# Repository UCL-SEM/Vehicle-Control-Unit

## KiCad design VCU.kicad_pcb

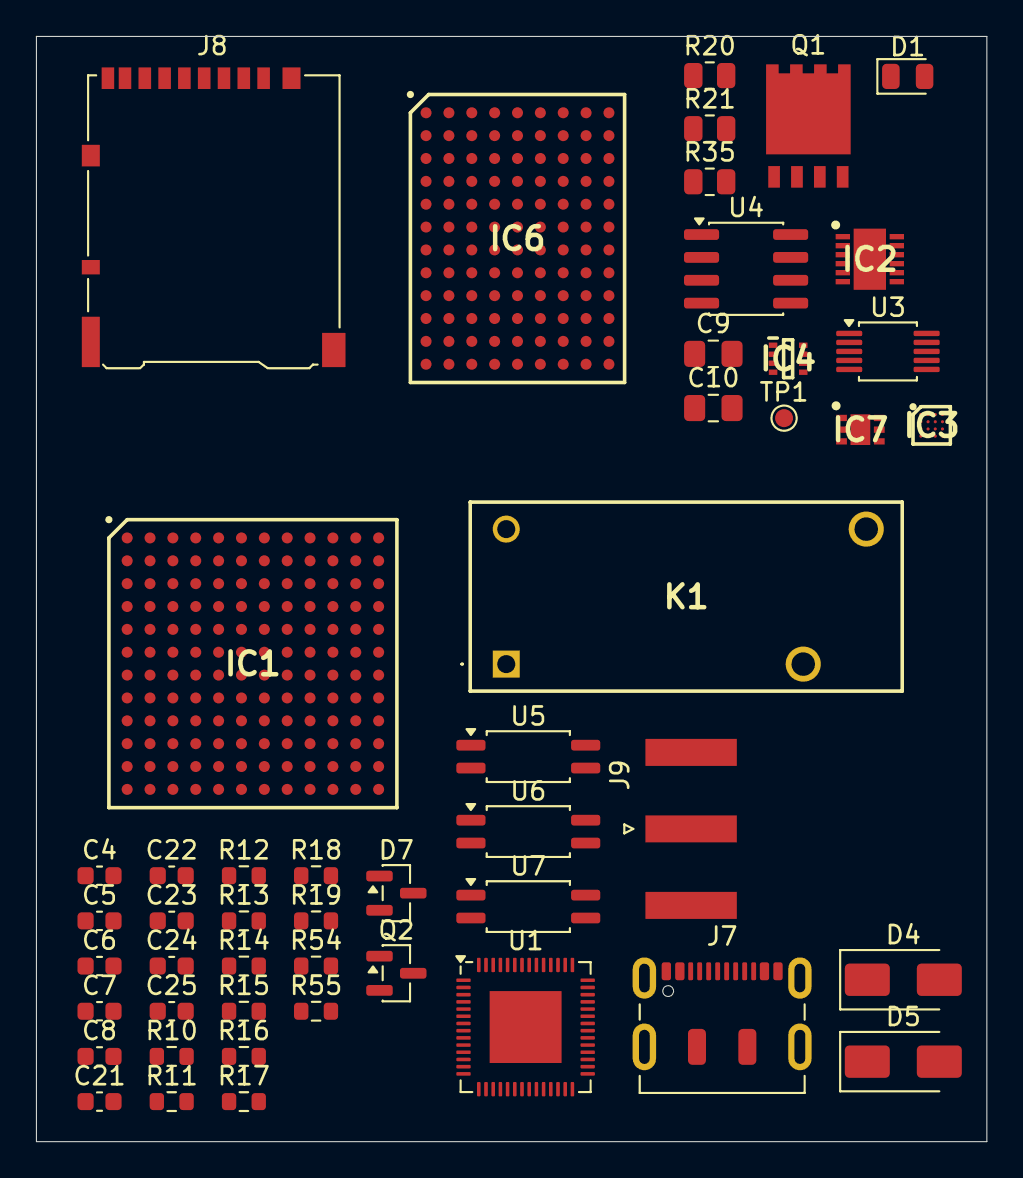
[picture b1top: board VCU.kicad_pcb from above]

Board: 2 copper layers, 52.8 x 61.4 mm, 50 parts (0 on the bottom side), 40 nets, no tracks yet.

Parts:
C4, C21, C24: 10uF; C_0603_1608Metric
C5, C6, C22, C23: 0.1uF; C_0603_1608Metric
C7, C8: 22uF; C_0603_1608Metric
C9: 0.1u; C_0805_2012Metric_Pad1.18x1.45mm_HandSolder
C10: 10u; C_0805_2012Metric_Pad1.18x1.45mm_HandSolder
C25: 47uF; C_0603_1608Metric
D1: LED; LED_0805_2012Metric
D4, D5: M7; D_SMA
D7: T24CAN; SOT-23
IC1: LTM4712IY#PBF; BGA144C127P12X12_1600X1600X868
IC2: LT4363IDE-1_PBF; SON50P300X400X80-13N-D
IC3: INA4235AIYBJR; BGA16C40P4X4_160X160X35
IC4: TPS2117DRLR; SOTFL50P160X60-8N
IC6: LTM8064IY; BGA108C127P9X12_1190X1600X512
IC7: TPS70933DRVR; SON65P200X200X80-7N
J7: DX07S016JA1R1500; USB_C_Receptacle_JAE_DX07S016JA1R1500
J8: DM3AT-SF-PEJM5; microSD_HC_Hirose_DM3AT-SF-PEJM5
J9: 132289; SMA_Amphenol_132289_EdgeMount
K1: G5PZ-1A-X_DC12; G5PZ1AXDC12
Q1: ISC015N06NM5LF2; PG-TDSON-8-FL
Q2: IRLML6344TRPBF; SOT-23
R10, R11: 5.1k; R_0603_1608Metric
R12, R13: 100k; R_0603_1608Metric
R14: 2.2k; R_0603_1608Metric
R15, R16, R17, R18, R19: 10k; R_0603_1608Metric
R20: 10k; R_0805_2012Metric
R21: 1k; R_0805_2012Metric
R35: 10M; R_0805_2012Metric
R54, R55: 60; R_0603_1608Metric
TP1: VBUS; TestPoint_Pad_D1.0mm
U1: ESP32-S3; QFN-56-1EP_7x7mm_P0.4mm_EP4x4mm
U3: INA238; TSSOP-10_3x3mm_P0.5mm
U4: ISO1640; SOIC-8_3.9x4.9mm_P1.27mm
U5, U6, U7: LTV-217-B-G; SOP-4_4.4x2.6mm_P1.27mm

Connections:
+3.3V: C4.1, C6.1, C7.1, C8.1, C23.1, C24.1, J8.4 (VDD), R15.1, R16.1, R17.1, R18.1, R19.1
+3V3: IC3.A4 (VS), IC3.B3 (EN), U4.1 (VCC1), U5.4, U6.4, U7.4
+5V: C21.1, C22.1
+13V: IC1.B4 (EXTVCC), IC6.H1 (VOUT), IC6.H2 (VOUT_1), IC6.H3 (VOUT_1), IC6.H4 (VOUT_1), IC6.J1 (VOUT_1), IC6.J2 (VOUT_1), IC6.J3 (VOUT_1), IC6.J4 (VOUT_1), IC6.K1 (VOUT_1), IC6.K2 (VOUT_1), IC6.K3 (VOUT_1), IC6.K4 (VOUT_1), IC6.L1 (VOUT_1), IC6.L2 (VOUT_1), IC6.L3 (VOUT_1), IC6.L4 (VOUT_1), IC6.M1 (VOUT_1), IC6.M2 (VOUT_1), IC6.M3 (VOUT_1), IC6.M4 (VOUT_1)
/FC_AUX: IC3.D2 (IN-4), IC6.A4 (RUN), IC6.A5 (VIN), IC6.A6 (VIN_1), IC6.A7 (VIN_1), IC6.A8 (VIN_1), IC6.A9 (VIN_1), IC6.B5 (VIN_1), IC6.B6 (VIN_1), IC6.B7 (VIN_1), IC6.B8 (VIN_1), IC6.B9 (VIN_1)
/FC_AUX_SNS+: IC3.D1 (IN+3), IC3.D3 (IN+4)
/FC_IN: IC1.A4 (ISP), IC2.2 (OUT), IC2.3 (SNS), Q1.1 (S)
/FC_SNS-: IC2.5 (VCC), IC2.8 (UV), IC3.A2 (IN-1), Q1.5 (D)
/H2_TTL: R21.1, U7.1
/MISO: J8.7 (DAT0), R19.2
/MOSI: J8.3 (CMD), R18.2
/RG_SNS+: IC1.H11 (VOUT), IC1.H12 (VOUT_2), IC1.J11 (VOUT_3), IC1.J12 (VOUT_4), IC1.K11 (VOUT_5), IC1.K12 (VOUT_6), IC1.L11 (VOUT_7), IC1.L12 (VOUT_8), IC1.M11 (VOUT_9), IC1.M12 (VOUT_10), IC3.A1 (IN+2)
/SCL: IC3.C4 (SCL), U4.3 (SCL1)
/SC_OUT: IC3.C1 (IN-3), K1.2 (COM)
/SDA: IC3.D4 (SDA), U4.2 (SDA1)
/SD_CS: J8.2 (DAT3/CD), R17.2
/SD_DET: C5.1, J8.9 (DET_B), J8.10 (DET_A), R15.2
/USB1_N: J7.A7 (D-), J7.B7 (D-)
/USB1_P: J7.A6 (D+), J7.B6 (D+)
/VBUS: J7.A4 (VBUS), J7.A9 (VBUS), J7.B4 (VBUS), J7.B9 (VBUS), R12.1, R14.1, TP1.1 (1_1)
/VBUS_DET: R12.2, R13.1
AUX_3V3: IC7.1 (OUT), U3.6 (VS), U4.8 (VCC2)
AUX_12V: C9.1, C10.1, IC7.6 (IN), U3.8 (Vbus), U3.9 (Vin-)
AUX_12V-S: D4.1 (K), D5.1 (K), K1.1 (COIL_1), U5.1
AUX_GND: C9.2, C10.2, IC7.3 (GND), IC7.7 (GND_2), Q2.2 (S), R20.2, R35.1, U3.7 (GND), U4.5 (GND2)
GND: C4.2, C5.2, C6.2, C7.2, C8.2, C21.2, C22.2, C23.2, C24.2, C25.2, D1.1 (K), D7.3 (A), IC1.A1 (GND), IC1.A2 (GND_2), IC1.A9 (PHMODE), IC1.A12 (GND_3), IC1.B1 (GND_4), IC1.B2 (GND_5), IC1.B7 (SGND), IC1.B12 (GND_6), IC1.C1 (GND_7), IC1.C2 (GND_8), IC1.C3 (GND_9), IC1.C4 (GND_10), IC1.C5 (GND_11), IC1.C6 (SGND_2), IC1.C7 (SGND_3), IC1.C8 (GND_12), IC1.C9 (GND_13), IC1.C10 (GND_14), IC1.C11 (GND_15), IC1.C12 (GND_16), IC1.D1 (GND_17), IC1.D2 (GND_18), IC1.D3 (GND_19), IC1.D4 (GND_20), IC1.D5 (GND_21), IC1.D6 (SGND_4), IC1.D7 (SGND_5), IC1.D8 (GND_22), IC1.D9 (GND_23), IC1.D10 (GND_24), IC1.D11 (GND_25), IC1.D12 (GND_26), IC1.E1 (GND_27), IC1.E2 (GND_28), IC1.E3 (GND_29), IC1.E4 (GND_30), IC1.E5 (GND_31), IC1.E6 (GND_32), IC1.E7 (GND_33), IC1.E8 (GND_34), IC1.E9 (GND_35), IC1.E10 (GND_36), IC1.E11 (GND_37), IC1.E12 (GND_38), IC1.F1 (GND_39), IC1.F2 (GND_40), IC1.F3 (GND_41), IC1.F4 (GND_42), IC1.F5 (GND_43), IC1.F6 (GND_44), IC1.F7 (GND_45), IC1.F8 (GND_46), IC1.F9 (GND_47), IC1.F10 (GND_48), IC1.F11 (GND_49), IC1.F12 (GND_50), IC1.G1 (GND_51), IC1.G2 (GND_52), IC1.G3 (GND_53), IC1.G4 (GND_54), IC1.G5 (GND_55), IC1.G6 (GND_56), IC1.G7 (GND_57), IC1.G8 (GND_58), IC1.G9 (GND_59), IC1.G10 (GND_60), IC1.G11 (GND_61), IC1.G12 (GND_62), IC1.H3 (GND_63), IC1.H4 (GND_64), IC1.H5 (GND_65), IC1.H6 (GND_66), IC1.H7 (GND_67), IC1.H8 (GND_68), IC1.H9 (GND_69), IC1.H10 (GND_70), IC1.J3 (GND_71), IC1.J4 (GND_72), IC1.J5 (GND_73), IC1.J6 (GND_74), IC1.J7 (GND_75), IC1.J8 (GND_76), IC1.J9 (GND_77), IC1.J10 (GND_78), IC1.K3 (GND_79), IC1.K4 (GND_80), IC1.K6 (GND_81), IC1.K7 (GND_82), IC1.K9 (GND_83), IC1.K10 (GND_84), IC1.L3 (GND_85), IC1.L4 (GND_86), IC1.L6 (GND_87), IC1.L7 (GND_88), IC1.L9 (GND_89), IC1.L10 (GND_90), IC1.M3 (GND_91), IC1.M4 (GND_92), IC1.M5 (GND_93), IC1.M6 (GND_94), IC1.M7 (GND_95), IC1.M8 (GND_96), IC1.M9 (GND_97), IC1.M10 (GND_98), IC2.7 (GND), IC2.9 (GND), IC2.13 (GND), IC3.B4 (GND), IC6.A1 (GND), IC6.B3 (GND_1), IC6.B4 (GND_1), IC6.C2 (GND_1), IC6.C3 (GND_1), IC6.C4 (GND_1), IC6.C5 (GND_1), IC6.C6 (GND_1), IC6.C7 (GND_1), IC6.C8 (GND_1), IC6.C9 (GND_1), IC6.D2 (GND_1), IC6.D3 (GND_1), IC6.D4 (GND_1), IC6.D5 (GND_1), IC6.D6 (GND_1), IC6.D7 (GND_1), IC6.D8 (GND_1), IC6.D9 (GND_1), IC6.E3 (GND_1), IC6.E4 (GND_1), IC6.E5 (GND_1), IC6.E6 (GND_1), IC6.E7 (GND_1), IC6.E8 (GND_1), IC6.E9 (GND_1), IC6.F1 (SYNC), IC6.F2 (MODE), IC6.F3 (GND_1), IC6.F4 (GND_1), IC6.F5 (GND_1), IC6.F6 (GND_1), IC6.F7 (GND_1), IC6.F8 (GND_1), IC6.F9 (GND_1), IC6.G1 (GND_1), IC6.G2 (GND_1), IC6.G3 (GND_1), IC6.G4 (GND_1), IC6.G5 (GND_1), IC6.G6 (GND_1), IC6.G7 (GND_1), IC6.G8 (GND_1), IC6.G9 (GND_1), IC6.H5 (GND_1), IC6.H6 (GND_1), IC6.H7 (GND_1), IC6.H8 (GND_1), IC6.H9 (GND_1), IC6.J5 (GND_1), IC6.J6 (GND_1), IC6.J7 (GND_1), IC6.J8 (GND_1), IC6.J9 (GND_1), IC6.K5 (GND_1), IC6.K6 (GND_1), IC6.K7 (GND_1), IC6.K8 (GND_1), IC6.K9 (GND_1), IC6.L5 (GND_1), IC6.L6 (GND_1), IC6.L7 (GND_1), IC6.L8 (GND_1), IC6.L9 (GND_1), IC6.M5 (GND_1), IC6.M6 (GND_1), IC6.M7 (GND_1), IC6.M8 (GND_1), IC6.M9 (GND_1), J7.A1 (GND), J7.A12 (GND), J7.B1 (GND), J7.B12 (GND), J8.6 (VSS), J9.2 (Ext), R10.2, R11.2, R13.2, R35.2, U1.57 (GND), U4.4 (GND1)
unnamed: C25.1, R54.2, R55.2
unnamed: D1.2 (A), R14.2
unnamed: D4.2 (A), D5.2 (A), K1.4 (COIL_2), Q2.3 (D)
unnamed: IC1.B10 (COMPA), IC1.B11 (COMPB)
unnamed: IC1.A3 (ISN), IC1.H1 (VIN), IC1.H2 (VIN_2), IC1.J1 (VIN_3), IC1.J2 (VIN_4), IC1.K1 (VIN_5), IC1.K2 (VIN_6), IC1.L1 (VIN_7), IC1.L2 (VIN_8), IC1.M1 (VIN_9), IC1.M2 (VIN_10)
unnamed: IC6.B1 (CTRL2), IC6.B2 (VREF), IC6.C1 (CTRL1)
unnamed: J7.A5 (CC1), R11.1
unnamed: J7.B5 (CC2), R10.1
unnamed: Q2.1 (G), R20.1, R21.2
unnamed: U1.2 (VDD3P3), U1.3 (VDD3P3)
unnamed: U1.55 (VDDA), U1.56 (VDDA)
unnamed: U3.5 (SCL), U4.6 (SCL2)
unnamed: U3.4 (SDA), U4.7 (SDA2)
unnamed: U5.2, U6.1
